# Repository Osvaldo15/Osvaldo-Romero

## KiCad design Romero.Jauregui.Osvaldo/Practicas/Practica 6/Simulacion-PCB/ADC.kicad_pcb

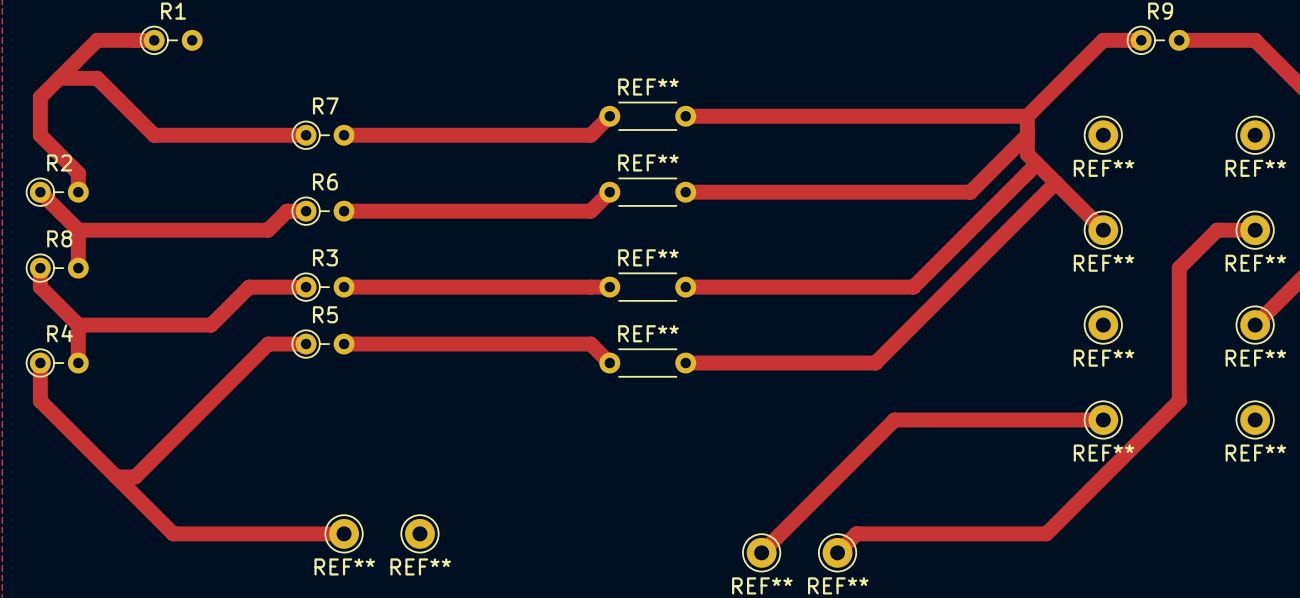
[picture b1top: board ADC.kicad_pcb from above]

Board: 2 copper layers, 9 parts (0 on the bottom side), 3 nets.

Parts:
R1, R2, R3, R4, R5, R6, R7, R8, R9: R; R_Axial_DIN0204_L3.6mm_D1.6mm_P2.54mm_Vertical

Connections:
unnamed: R1.1, R4.2, R8.2
unnamed: R1.2, R2.1, R5.2
unnamed: R2.2, R3.1, R6.2

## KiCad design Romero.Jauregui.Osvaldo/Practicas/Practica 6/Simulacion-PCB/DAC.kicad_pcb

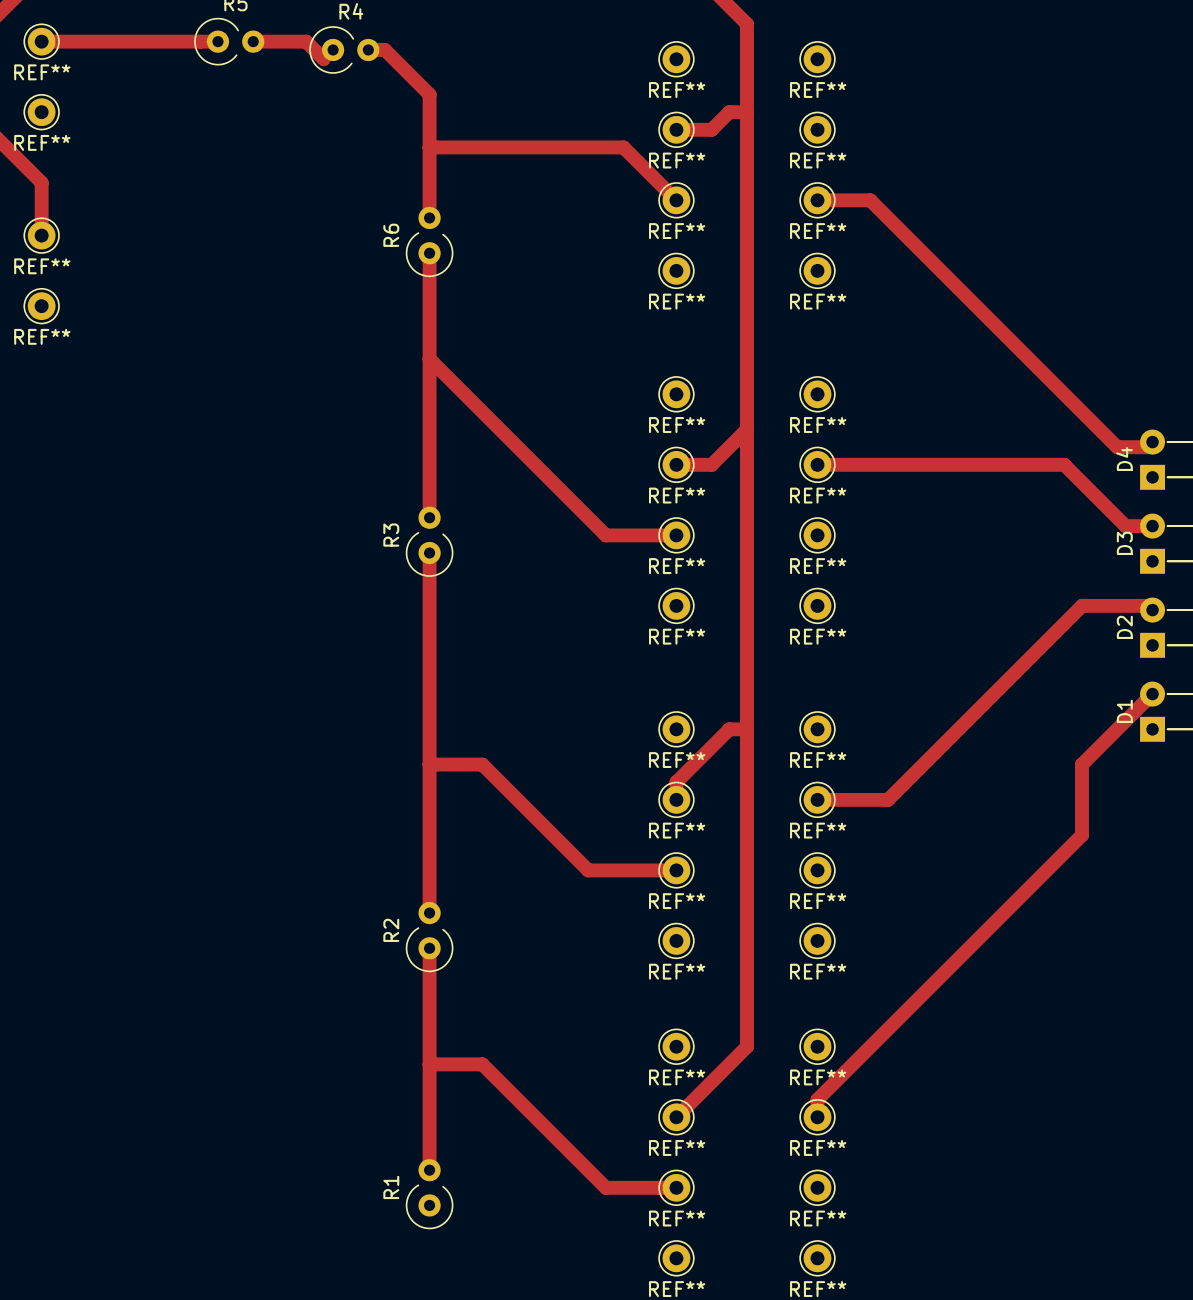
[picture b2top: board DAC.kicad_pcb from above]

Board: 2 copper layers, 10 parts (0 on the bottom side), 3 nets.

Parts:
D1, D2, D3, D4: LED; LED_D1.8mm_W1.8mm_H2.4mm_Horizontal_O6.35mm_Z4.9mm
R1, R2, R3, R4, R5, R6: R; R_Axial_DIN0309_L9.0mm_D3.2mm_P2.54mm_Vertical

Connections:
unnamed: R1.1, R2.2
unnamed: R2.1, R3.1
unnamed: R3.2, R4.1
